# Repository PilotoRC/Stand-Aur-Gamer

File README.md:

# Stand-Aur-Gamer
Stan para sostener auriculares Gamer, con Led RGB Neopixel en las patas de apoyo, contro WIFI app celular 

ESTOY APRENDIENDO A USAR GITHUB PARA ORDENAR MIS PROYECTOS Y PODER COMPARTIR

LA impresion 3D autos https://www.thingiverse.com/thing:2050885

Estructura del repositorio
EJEMPLO que encontre en español
Raiz: Fuentes del proyecto de la placa de circuito impreso para el software de diseño de PCB KiCad.
Gerber : Ficheros de fabricacion en formato Gerber de la placa de circuito impreso.
Imagenes : Renders de la placa de circuito impreso.
Pdf : Ficheros para el montaje en formato pdf. Esquema del circuito, situacion de componentes, etc.
Modelos3D : Modelos 3D en formato .wrl para la visualizacion en el proyecto del diseño de la PCB.
Soft/lib : Librerías para el uso de los distintos elementos presentes en la placa.
Soft/src : Ejemplos de uso de la placa.

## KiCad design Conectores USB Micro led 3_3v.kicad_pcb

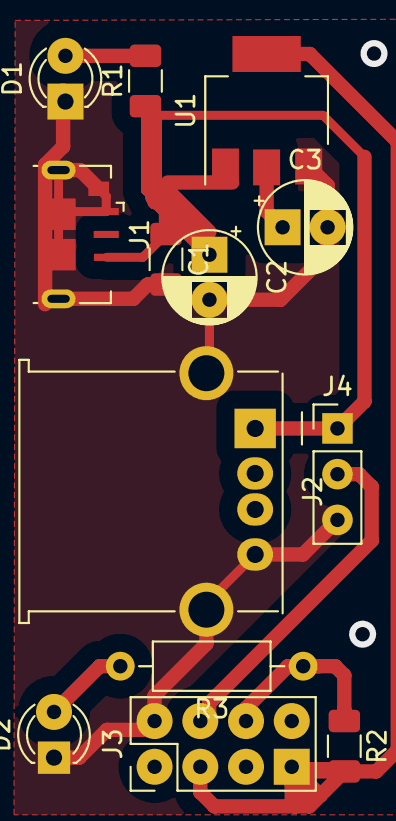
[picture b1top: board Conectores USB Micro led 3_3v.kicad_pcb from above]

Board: 2 copper layers, 13 parts (0 on the bottom side), 7 nets.

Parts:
C1: C; C_1206_3216Metric
C2: 10uF; CP_Radial_D5.0mm_P2.50mm
C3: 47uF; CP_Radial_D5.0mm_P2.50mm
D1: ROJO ON; LED_D3.0mm_IRGrey
D2: AZUL LINK; LED_D3.0mm_IRGrey
J1: USB_B_Micro; USB_Micro-B_GCT_USB3076-30-A
J2: USB_A; USB_A_Molex_67643_Horizontal
J3: ESP01; PinHeader_2x04_P2.54mm_Vertical
J4: RGB Neo; PinHeader_1x03_P2.54mm_Vertical
R1: 330; R_1206_3216Metric
R2: 10K; R_1206_3216Metric
R3: R; R_Axial_DIN0207_L6.3mm_D2.5mm_P10.16mm_Horizontal
U1: AP1117-33; SOT-223-3_TabPin2

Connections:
+3V3: C3.1, J3.3, J3.7, R2.2, U1.2
+5V: C1.1, C2.1, J1.1, J2.1, J4.1, R1.1, U1.3
/GPIO00-FLASH: J3.6, R2.1, R3.1
GND: C1.2, C2.2, C3.2, D1.1, D2.1, J1.5, J1.6, J2.4, J2.5, J3.2, J4.3, U1.1
unnamed: D1.2, R1.2
unnamed: D2.2, R3.2
S: J3.4, J4.2

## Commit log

2020-10-25 Update README.md
    Imagenes
2020-10-25 PCB V3.3 KICAD
